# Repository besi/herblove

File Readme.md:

Herblove
========

Connect a PET bottle to a water drip adapter and keep your herbs happy.

## Features

- Control a 12V valve
- Battery powered with solar charging
- Measure temperature and humidity
- Log data onto an SD card
- Read a floating sensor
- Two buttons
- Onboard Neopixel

## Pinout

| Pin | Function    |
|-----|-------------|
| 2   | Enable 12V  |
| 10  | I2C SCL     |
| 8   | I2C SDA     |
| 1   | SPI MISO    |
| 4   | SPI MOSI    |
| 0   | SPI CLK     |
| 5   | SPI CS      |
| 6   | Buttons ADC |
| 3   | ADC Battery |
| 7   | Neopixel    |

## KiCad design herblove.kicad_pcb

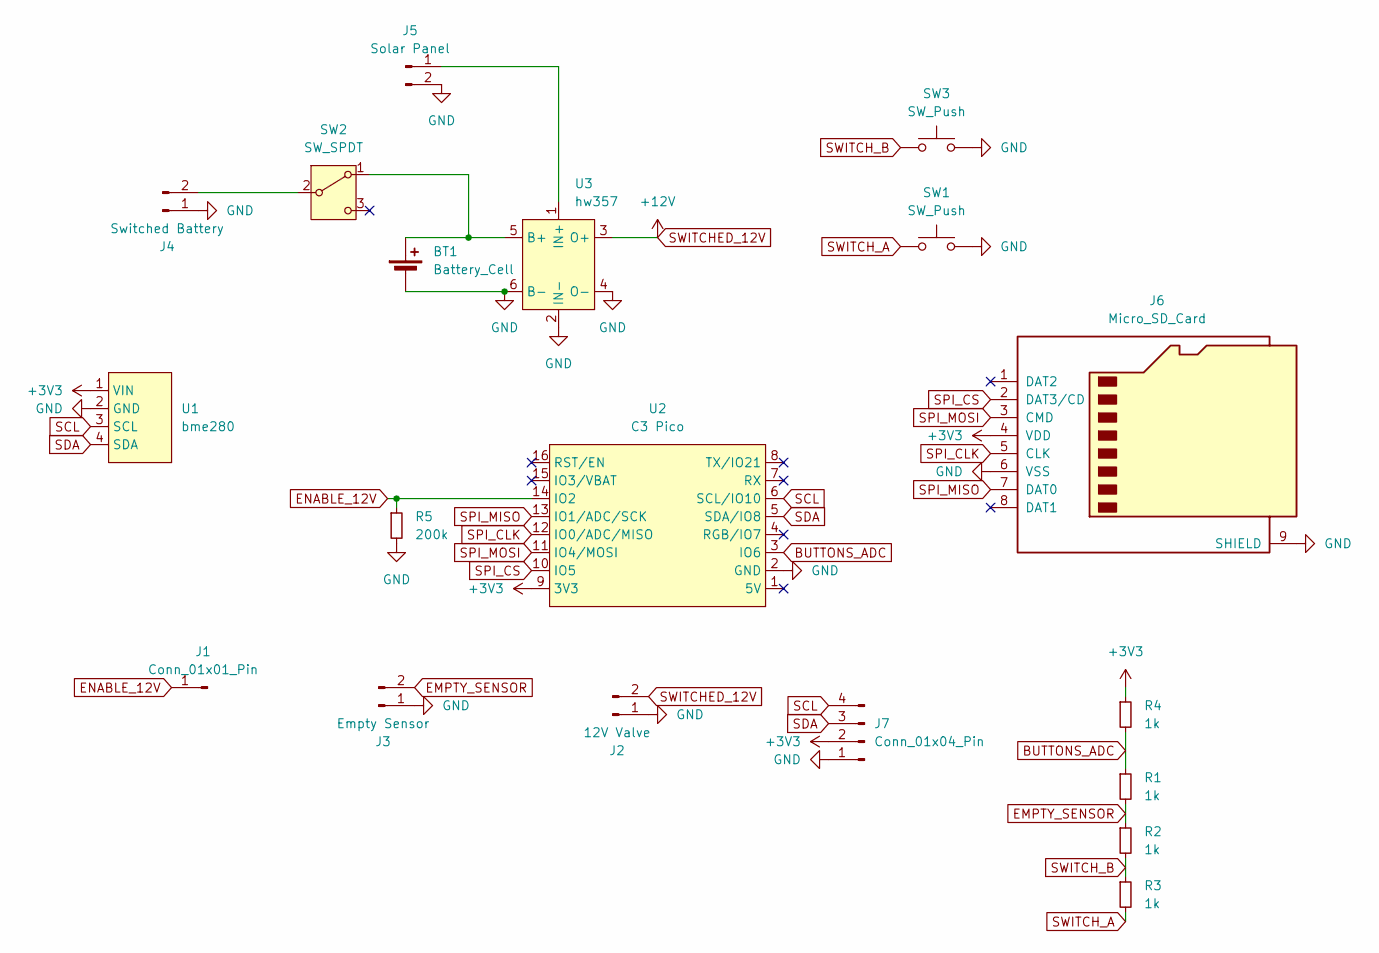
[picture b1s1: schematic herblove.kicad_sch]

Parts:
BT1: Battery_Cell; JST_PH_B2B-PH-K_1x02_P2.00mm_Vertical
J1: Conn_01x01_Pin; PinHeader_1x01_P2.54mm_Vertical
J2: 12V Valve; PinHeader_1x02_P2.54mm_Vertical
J3: Empty Sensor; PinHeader_1x02_P2.54mm_Vertical
J4: Switched Battery; JST_PH_B2B-PH-K_1x02_P2.00mm_Vertical
J5: Solar Panel; JST_PH_B2B-PH-K_1x02_P2.00mm_Vertical
J6: Micro_SD_Card; sd-card
J7: Conn_01x04_Pin; PinHeader_1x04_P2.54mm_Vertical
R1, R2, R3, R4: 1k; R_Axial_DIN0207_L6.3mm_D2.5mm_P7.62mm_Horizontal
R5: 200k; R_Axial_DIN0207_L6.3mm_D2.5mm_P7.62mm_Horizontal
SW1, SW3: SW_Push; pts636
SW2: SW_SPDT; as12ap
U1: bme280
U2: C3 Pico; c3-pico
U3: hw357

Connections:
+3V3: J6.4 (VDD), J7.2, R4.1, U1.1 (VIN), U2.9 (3V3)
BUTTONS_ADC: R1.1, R4.2, U2.3 (IO6)
EMPTY_SENSOR: J3.2, R1.2, R2.1
ENABLE_12V: J1.1, R5.1, U2.14 (IO2)
GND: BT1.2 (-), J2.1, J3.1, J4.1, J5.2, J6.6 (VSS), J6.9 (SHIELD), J7.1, R5.2, SW1.2, SW3.2, U1.2 (GND), U2.2 (GND), U3.2 (IN-), U3.4 (O-), U3.6 (B-)
unnamed: BT1.1 (+), SW2.1 (A), U3.5 (B+)
unnamed: J4.2, SW2.2 (B)
unnamed: J5.1, U3.1 (IN+)
SCL: J7.4, U1.3 (SCL), U2.6 (SCL/IO10)
SDA: J7.3, U1.4 (SDA), U2.5 (SDA/IO8)
SPI_CLK: J6.5 (CLK), U2.12 (IO0/ADC/MISO)
SPI_CS: J6.2 (DAT3/CD), U2.10 (IO5)
SPI_MISO: J6.7 (DAT0), U2.13 (IO1/ADC/SCK)
SPI_MOSI: J6.3 (CMD), U2.11 (IO4/MOSI)
SWITCHED_12V: J2.2, U3.3 (O+)
SWITCH_A: R3.2, SW1.1
SWITCH_B: R2.2, R3.1, SW3.1

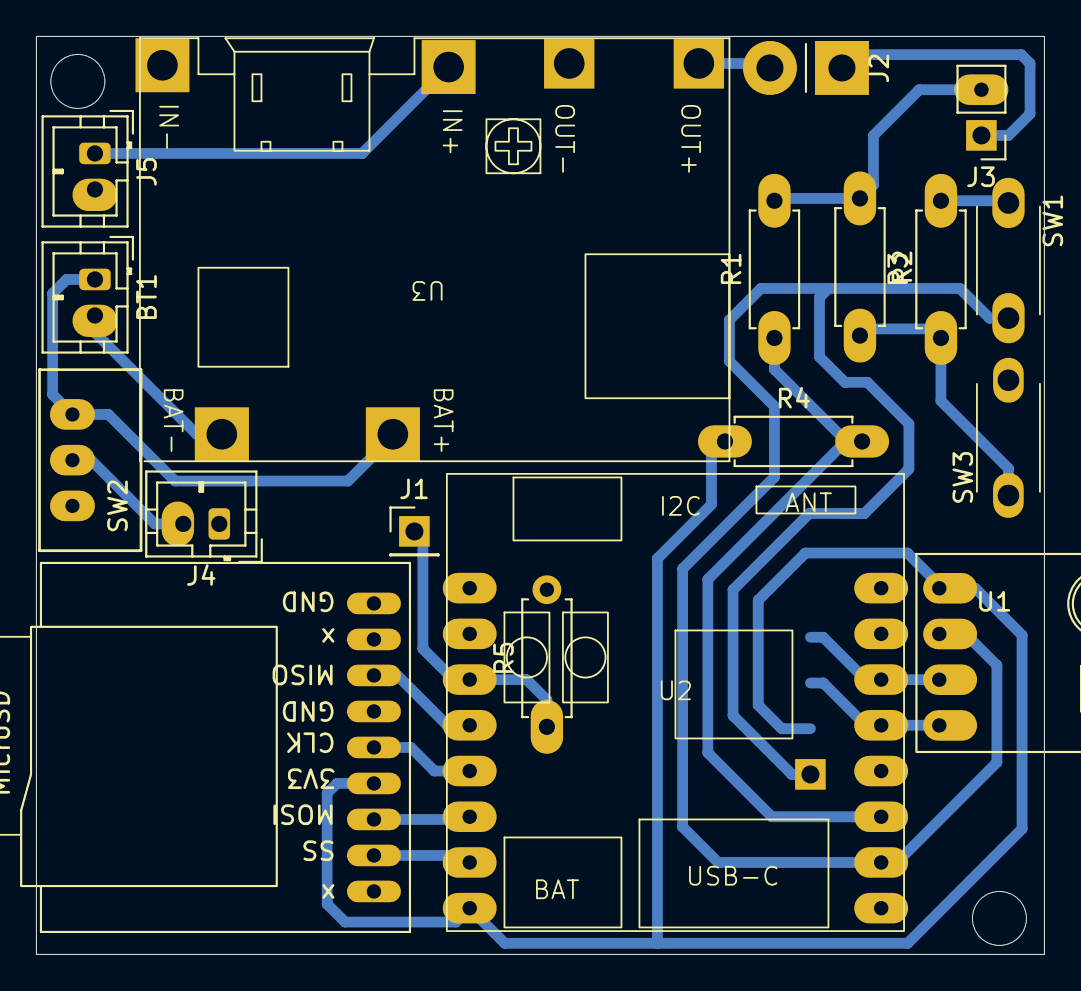
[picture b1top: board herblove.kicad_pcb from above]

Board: 2 copper layers, 56.0 x 51.0 mm, 19 parts (1 on the bottom side), 17 nets.
